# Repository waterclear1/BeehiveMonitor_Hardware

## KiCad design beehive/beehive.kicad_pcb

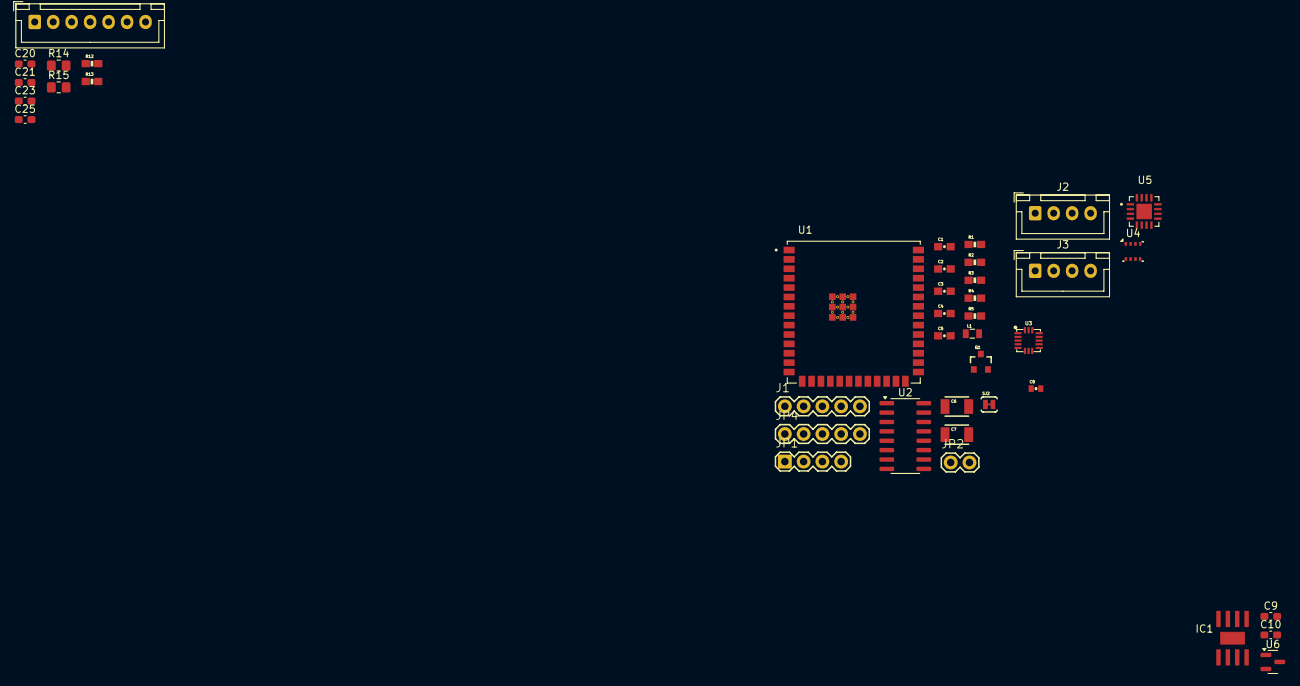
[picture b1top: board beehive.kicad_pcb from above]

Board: 2 copper layers, 40 parts (0 on the bottom side), 33 nets, no tracks yet.

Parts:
C1, C2, C3, C4, C5: 0.1uF; 0603-CAP
C6, C7: 10uF; 1210
C8: 0.1uF; 0402-CAP
C9, C10: 10uF/25V; C_0603_1608Metric_Pad1.08x0.95mm_HandSolder
C20, C21, C23, C25: 10uF; C_0603_1608Metric_Pad1.08x0.95mm_HandSolder
IC1: MP2307; SO8-TH
J1: M05PTH; 1X05
J2, J3: Conn_01x04_Pin; JST_XH_B4B-XH-A_1x04_P2.50mm_Vertical
J4: Conn_01x07_Socket; JST_XH_B7B-XH-A_1x07_P2.50mm_Vertical
JP1: M04PTH; 1X04
JP2: M02PTH; 1X02
JP4: M05PTH; 1X05
L1: 3.3uH; 0805
Q1: MMBT4403; SOT23-3
R1: 20k; 0603-RES
R2: 8.2K; 0603-RES
R3, R4, R13: 100; 0603-RES
R5: 10K; 0603-RES
R12: 10k; 0603-RES
R14, R15: 5.1k; R_0805_2012Metric_Pad1.20x1.40mm_HandSolder
SJ2: JUMPER-PAD-2-NC_BY_TRACE; PAD-JUMPER-2-NC_BY_TRACE_YES_SILK
U1: ESP32-S3-WROOM-1U; XCVR_ESP32-S3-WROOM-1U
U2: HX711; SOP-16_3.9x9.9mm_P1.27mm
U3: ADXL362; LGA-16-3X2.5
U4: BME280; Bosch_LGA-8_2.5x2.5mm_P0.65mm_ClockwisePinNumbering
U5: TP5100; QFN65P400X400X90-17N
U6: MCP1700x-330xxTT; SOT-23

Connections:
+3.3V: C8.2, C25.1, J2.1, J4.1, R12.1, U1.2 (3V3), U3.P$1 (VDDIO), U3.P$14 (VS), U6.2 (VO)
+12V: C20.1, U5.1 (VIN), U5.4 (VIN), U5.5 (VIN), U5.16 (VIN)
+BATT: C9.1, C10.1, IC1.2 (IN)
/A+: JP4.2, R4.1
/A-: JP4.3, R3.1
/AVDD: C3.1, C7.1, JP4.5, L1.1
/B+: JP2.1, U2.10 (INB+)
/B-: JP2.2, U2.9 (INB-)
/DAT: J1.3, U2.12 (DOUT)
BOOT: R13.1, U1.27 (IO0)
EN: R12.2, U1.3 (EN)
GND: C2.1, C3.2, C4.2, C5.2, C6.2, C7.2, C8.1, C9.2, C10.2, C20.2, C21.2, C23.2, C25.2, IC1.4 (GND), J1.5, J2.2, J4.2, JP4.1, JP4.4, R2.1, R14.2, R15.2, SJ2.1, U1.1 (GND), U1.40 (GND), U1.41_1 (GND), U1.41_2 (GND), U1.41_3 (GND), U1.41_4 (GND), U1.41_5 (GND), U1.41_6 (GND), U1.41_7 (GND), U1.41_8 (GND), U1.41_9 (GND), U2.5 (AGND), U2.14 (XI), U3.P$12 (GND), U3.P$13 (GND), U3.P$16 (GND), U5.7 (GND), U5.11 (TS), U5.17 (EXP)
unnamed: C21.1, U5.9 (BAT)
unnamed: U5.10 (VREG), U5.12 (RTRICK), U5.13 (CS)
unnamed: IC1.3 (SW), U6.3 (VI)
unnamed: J2.3, U3.P$11 (INT1)
unnamed: J2.4, U3.P$9 (INT2)
unnamed: J3.1, U3.P$8 (~CS)
unnamed: J3.2, U3.P$7 (MISO)
unnamed: J3.3, U3.P$6 (MOSI)
unnamed: J3.4, U3.P$4 (SCLK)
unnamed: U5.2 (LX), U5.3 (LX)
unnamed: Q1.1 (B), U2.2 (BASE)
unnamed: L1.2, Q1.3 (C), R1.2, U2.3 (AVDD)
unnamed: C1.2, R4.2, U2.8 (INA+)
unnamed: C1.1, R3.2, U2.7 (INA-)
unnamed: R5.1, SJ2.2, U2.15 (RATE)
unnamed: C2.2, U2.6 (VBG)
unnamed: R1.1, R2.2, U2.4 (VFB)
unnamed: C23.1, U5.8 (VS)
SCK: J1.4, J4.4, U2.11 (PD_SCK)
VCC: C5.1, C6.1, J1.2, Q1.2 (E), R5.2, U2.1 (VSUP)
VDD: C4.1, J1.1, U2.16 (DVDD)

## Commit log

2025-07-29 added custom library submodule
2025-09-16 TP5100 and ESP32 remaining
2025-09-30 change connection from the sensor block
2025-11-01 last
